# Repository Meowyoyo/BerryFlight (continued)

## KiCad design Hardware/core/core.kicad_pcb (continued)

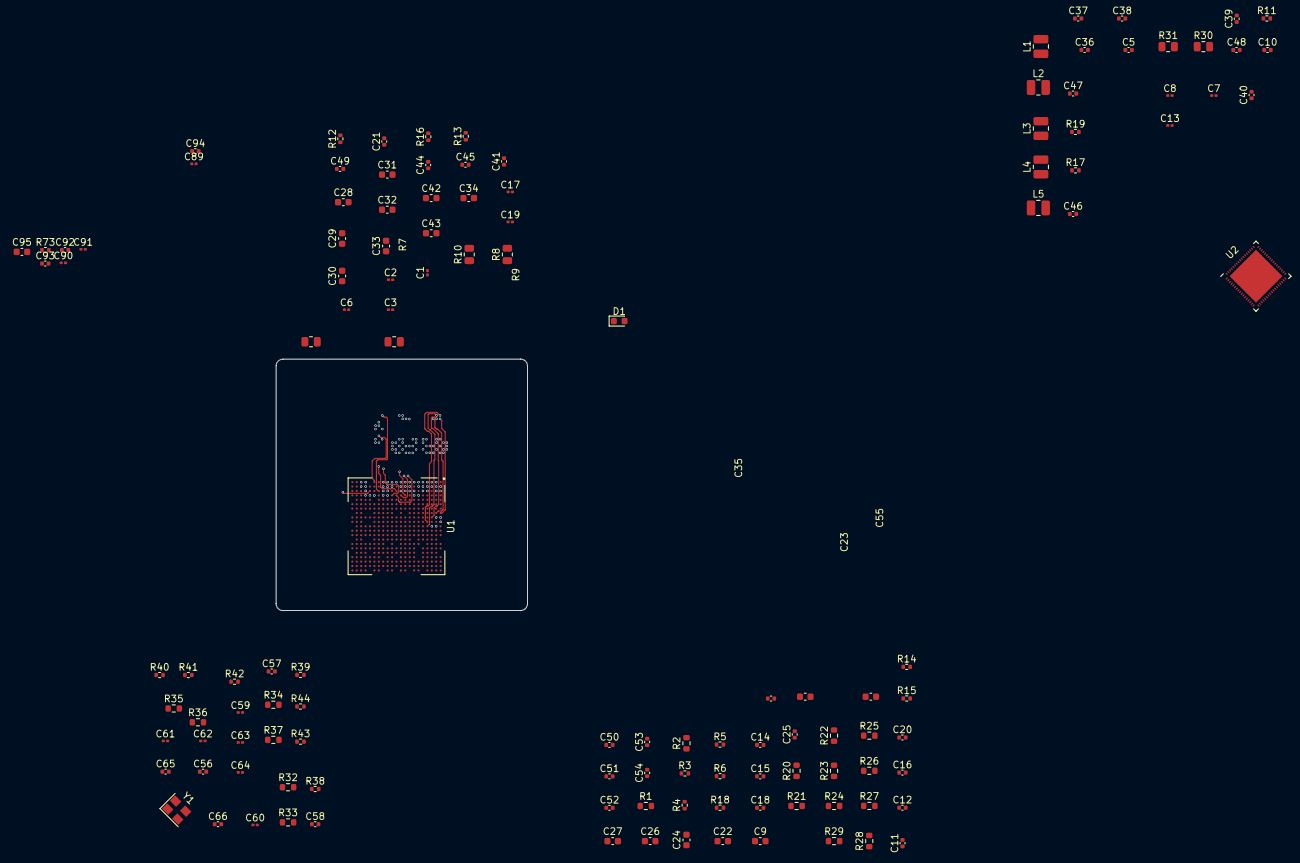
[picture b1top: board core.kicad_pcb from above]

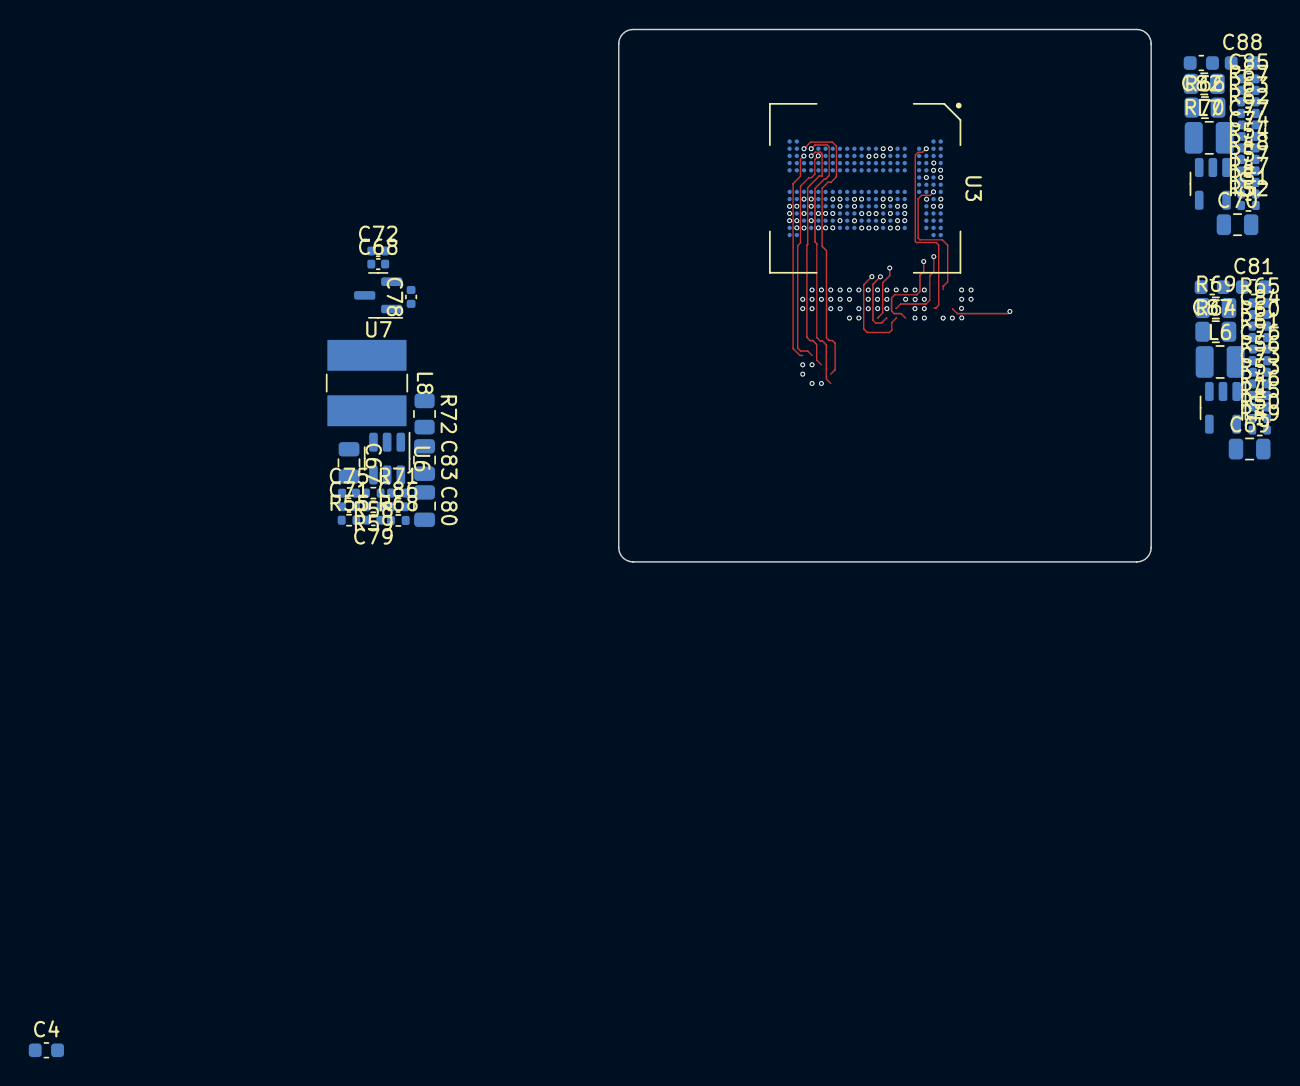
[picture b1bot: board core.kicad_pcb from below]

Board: 6 copper layers, 185 parts (59 on the bottom side), 156 nets.

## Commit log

2021-03-26 Docs
2021-03-26 more docs
2021-03-26 docs...
2021-03-26 test
2021-03-26 grrr
2021-03-29 readme update RV1126
2021-03-29 logo
2021-03-29 add telegram group
2021-04-13 PMIC wireup
2021-04-13 Create LICENSE
2021-04-14 osc pll pmuio
2021-04-15 moooaaarr power
2021-04-15 eMCP
2021-05-04 no ram yet
2021-05-05 byte0?
2021-05-05 byte0...
2021-05-20 byte1 and 2
2021-05-21 byte3 and address
